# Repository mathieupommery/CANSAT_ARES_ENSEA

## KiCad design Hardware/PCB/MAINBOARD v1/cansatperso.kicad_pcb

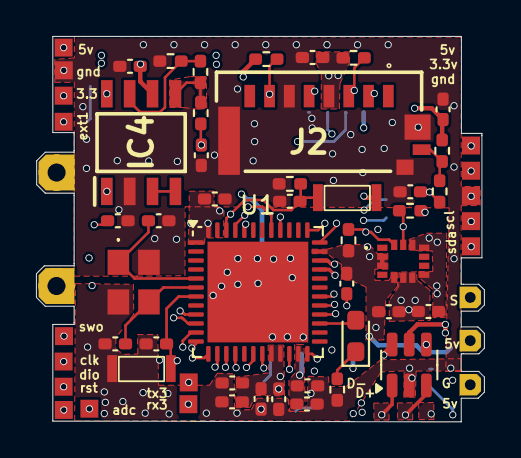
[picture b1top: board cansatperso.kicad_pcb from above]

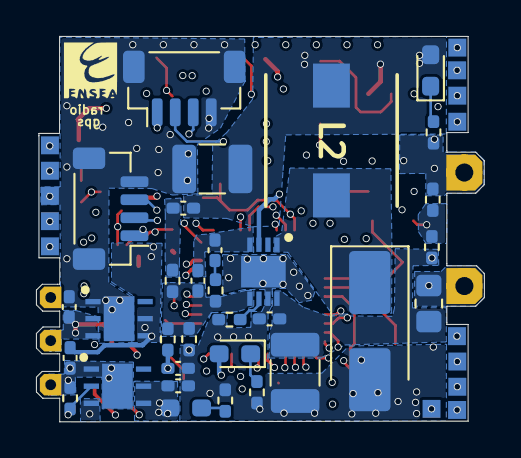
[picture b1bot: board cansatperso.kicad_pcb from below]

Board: 6 copper layers, 24.9 x 21.4 mm, 85 parts (34 on the bottom side), 44 nets.

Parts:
1, 1#2, 2, 2#2, 3, 3#2, 3#3, 4, 5, 6, 7, 7#2, 8: (no value)
C1, C4, C5, C6, C9, C16, C30: 100n; C_0402_1005Metric_Pad0.74x0.62mm_HandSolder
C2: 0.1u; C_0402_1005Metric_Pad0.74x0.62mm_HandSolder
C3, C7, C14, C32: 10n; C_0402_1005Metric_Pad0.74x0.62mm_HandSolder
C8, C10, C18, C19, C20, C21, C31: 1u; C_0402_1005Metric_Pad0.74x0.62mm_HandSolder
C11, C15: 4.7u; C_0402_1005Metric_Pad0.74x0.62mm_HandSolder
C12, C13: 16p; C_0402_1005Metric_Pad0.74x0.62mm_HandSolder
C17: 10u; C_0402_1005Metric_Pad0.74x0.62mm_HandSolder
C24: 10u; C_1210_3225Metric_Pad1.33x2.70mm_HandSolder
C25: 470n; C_0402_1005Metric_Pad0.74x0.62mm_HandSolder
C26: 22n; C_0402_1005Metric_Pad0.74x0.62mm_HandSolder
C27: 220p; C_0402_1005Metric_Pad0.74x0.62mm_HandSolder
C28: 3.3n; C_0402_1005Metric_Pad0.74x0.62mm_HandSolder
C29: 22u; C_1210_3225Metric_Pad1.33x2.70mm_HandSolder
D1, D3, D4, D5: LED; LED_0603_1608Metric_Pad1.05x0.95mm_HandSolder
D2: STPS3L40; D_SMB_Handsoldering
IC1: 2536030320001
IC2, IC5: LDO40LPU33RY; SON95P300X300X90-7N-D
IC3: L7981TR; SON50P300X300X100-9N-D
IC4: TSC102IDT; SOIC127P600X175-8N
J2: 47309-2651
J3: connecteur gps; JST_SH_BM04B-SRSS-TB_1x04-1MP_P1.00mm_Vertical
J4: connecteur radio; JST_SH_BM04B-SRSS-TB_1x04-1MP_P1.00mm_Vertical
L2: 22u; INDPM7373X340N
R1: 100k; R_0402_1005Metric_Pad0.72x0.64mm_HandSolder
R2, R5, R6, R22: 10k; R_0402_1005Metric_Pad0.72x0.64mm_HandSolder
R3, R17: 200R; R_0402_1005Metric_Pad0.72x0.64mm_HandSolder
R4, R11, R26: 1k; R_0402_1005Metric_Pad0.72x0.64mm_HandSolder
R7, R8, R9, R10: 47k; R_0402_1005Metric_Pad0.72x0.64mm_HandSolder
R15: 220k; R_0402_1005Metric_Pad0.72x0.64mm_HandSolder
R16: 3.3k; R_0402_1005Metric_Pad0.72x0.64mm_HandSolder
R18: 4.99k; R_0402_1005Metric_Pad0.72x0.64mm_HandSolder
R19: 680R; R_0402_1005Metric_Pad0.72x0.64mm_HandSolder
R20: 1.1k; R_0402_1005Metric_Pad0.72x0.64mm_HandSolder
R21: 20k; R_0402_1005Metric_Pad0.72x0.64mm_HandSolder
R23: 10m; R_0805_2012Metric_Pad1.20x1.40mm_HandSolder
R24: 100R; R_0402_1005Metric_Pad0.72x0.64mm_HandSolder
R25: 2k; R_0402_1005Metric_Pad0.72x0.64mm_HandSolder
SW1: RSTBTN; SW_KXT3
SW2: boot; SW_KXT3
U1: STM32G431CBUx; QFN-48-1EP_7x7mm_P0.5mm_EP5.6x5.6mm
U2: USBLC6-2SC6; SOT-23-6
Y1: Crystal_GND24_Small; MCSJK7U1200101080B10

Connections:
3.3VEN: C21.1, D4.2 (A), IC5.4 (VOUT), IC5.5 (VSENSE), J3.1, J4.1
+3.3V: 2.1, 7.1, 7#2.1, C1.1, C4.2, C5.2, C6.2, C7.2, C8.2, C9.2, C10.2, C11.1, C15.1, C16.1, C17.1, C20.1, D5.2 (A), IC1.2 (RSVD_1), IC1.3 (RSVD_2), IC1.5 (VDD_IO), IC1.8 (VDD), IC1.11 (RSVD_4), IC1.12 (CS), IC2.4 (VOUT), IC2.5 (VSENSE), J2.4, R5.1, R7.1, R8.1, R9.1, R10.2, SW2.2, U1.1 (VBAT), U1.20 (VREF+), U1.21 (VDDA), U1.23 (VDD), U1.35 (VDD), U1.48 (VDD)
+5V: 8.1, C18.1, C19.1, C28.1, C29.1, C31.1, D1.2 (A), IC2.2 (EN), IC2.3 (VIN), IC4.6 (VCC), IC5.3 (VIN), L2.2, R18.1, U2.5 (VBUS)
ADC1_IN2_CURR: C32.2, R24.1, U1.9 (PA1)
ADC1_IN3_VBAT: C30.2, R21.1, R22.2, U1.10 (PA2)
BAT+: IC4.8 (VP), R23.2
D+: U1.34 (PA12), U2.4 (I/O2)
D-: U1.33 (PA11), U2.6 (I/O1)
GND: 1.1, 6.1, C1.2, C2.1, C3.1, C4.1, C5.1, C6.1, C7.1, C8.1, C9.1, C10.1, C11.2, C12.2, C13.1, C14.2, C15.2, C16.2, C17.2, C18.2, C19.2, C20.2, C21.2, C24.2, C25.2, C29.2, C30.1, C31.2, C32.1, D2.2 (A), IC1.6 (GND_1), IC1.7 (GND_2), IC2.1 (GND), IC2.7 (EP), IC3.7 (GND), IC3.9 (EP), IC4.2 (GND), IC5.1 (GND), IC5.7 (EP), J2.6, J2.9 (G1), J2.10 (G2), J2.12 (G4), J3.4, J3.MP, J4.4, J4.MP, R1.2, R2.2, R3.1, R4.1, R11.1, R15.2, R19.2, R20.1, R22.1, R26.1, SW1.1, U1.49 (VSS), U2.2 (GND), Y1.2, Y1.4
GPIO_EXTI1: 3.1, U1.18 (PB1)
I2C3_SCL_ACCEL: 4.1, IC1.13 (SCL), R9.2, U1.30 (PA8)
I2C3_SDA_ACCEL: 5.1, IC1.14 (SDA), R10.1, U1.40 (PC11)
LPUART1_RX_RADIO: J4.2, U1.11 (PA3)
LPUART1_TX_RADIO: J4.3, U1.24 (PB11)
NRST: 3#2.1, 3#3.1, C2.2, SW1.2, U1.7 (PG10)
unnamed: C26.2, R16.1
unnamed: C28.2, R17.1
unnamed: D1.1 (K), R3.2
unnamed: D2.1 (K), IC3.1 (OUT), L2.1
unnamed: D3.2 (A), U1.27 (PB14)
unnamed: D3.1 (K), R20.2
unnamed: D4.1 (K), R4.2
unnamed: D5.1 (K), R11.2
unnamed: C26.1, C27.1, IC3.4 (COMP)
unnamed: C27.2, IC3.5 (FB), R16.2, R17.2, R18.2, R19.1
unnamed: IC3.6 (FSW), R15.1
unnamed: IC4.3 (A1), IC4.4 (A2)
unnamed: IC4.7 (A3), R25.1, R26.2
unnamed: IC4.5 (OUT), R24.2, R25.2
unnamed: J2.11 (G3), R5.2, R6.1
unnamed: C13.2, U1.5 (PF0), Y1.1
unnamed: C12.1, U1.6 (PF1), Y1.3
PWEN: IC5.2 (EN), R1.1, U1.28 (PB15)
SDDETECT: C14.1, R6.2, U1.19 (PB2)
SPI1_CS_SD: J2.2, U1.16 (PC4)
SPI1_MISO_SD: J2.7, R8.2, U1.14 (PA6)
SPI1_MOSI_SD: J2.3, R7.2, U1.15 (PA7)
SPI1_SCK_SD: J2.5, U1.13 (PA5)
SWCLK/I2C1_SDA: 1#2.1, U1.37 (PA14)
SWDIO: 2#2.1, U1.36 (PA13)
USART1_RX_GPS: J3.2, U1.45 (PB7)
USART1_TX_GPS: J3.3, U1.44 (PB6)
USART3_RX: C3.2, R2.1, SW2.1, U1.46 (PB8)
VIN: C24.1, C25.1, IC3.3 (EN), IC3.8 (V_CC), IC4.1 (VM), R21.2, R23.1

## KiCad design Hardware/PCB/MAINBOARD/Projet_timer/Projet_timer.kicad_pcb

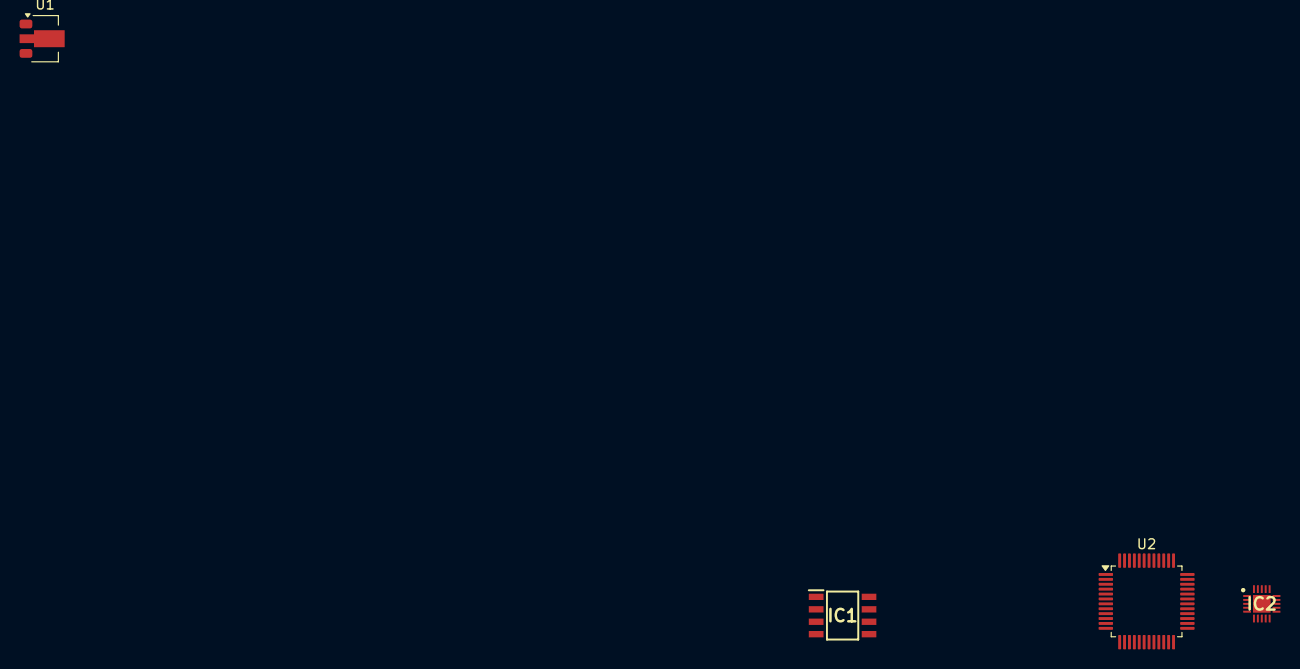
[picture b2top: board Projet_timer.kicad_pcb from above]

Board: 2 copper layers, 4 parts (0 on the bottom side), 3 nets, no tracks yet.

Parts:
IC1: AP1509-50SG-13; SOIC127P600X170-8N
IC2: TMC6300-LA-T; QFN40P300X300X90-21N
U1: AP130-33Y; SOT-89-3
U2: STM32G431C6Tx; LQFP-48_7x7mm_P0.5mm

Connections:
+8V: IC1.1 (VIN), U1.3 (VI)
GND: IC1.4 (SD), IC1.5 (GND_1), IC1.6 (GND_2), IC1.7 (GND_3), IC1.8 (GND_4), U1.2 (GND)
unnamed: U2.23 (VSS), U2.35 (VSS), U2.47 (VSS)

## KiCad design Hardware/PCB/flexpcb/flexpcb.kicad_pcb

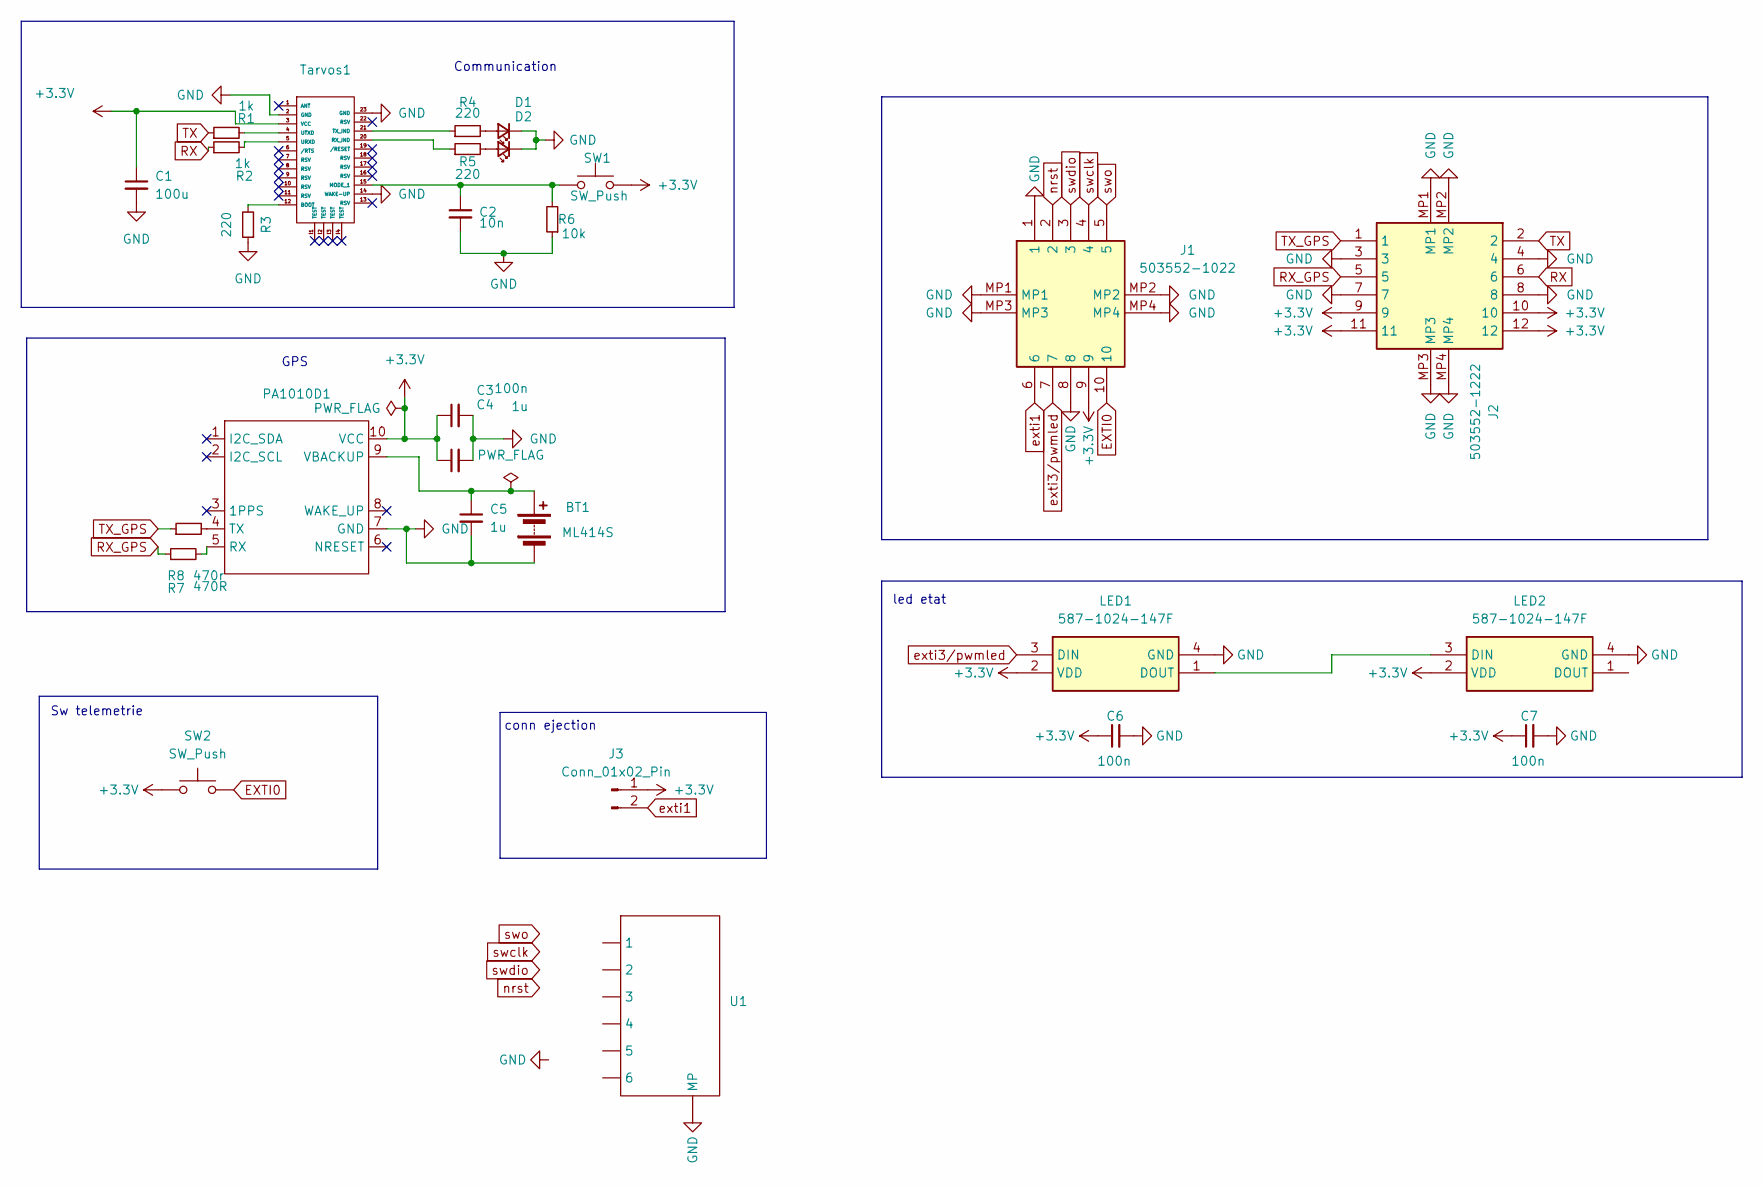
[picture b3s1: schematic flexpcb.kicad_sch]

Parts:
BT1: ML414S; MS421R-IV03E
C1: 100u; C_0805_2012Metric_Pad1.18x1.45mm_HandSolder
C2: 10n; C_0402_1005Metric
C3, C6, C7: 100n; C_0402_1005Metric
C4: 1u; C_0402_1005Metric
C5: 1u; C_0402_1005Metric_Pad0.74x0.62mm_HandSolder
D1, D2: LED_Small; LED_0603_1608Metric
J1: 503552-1022; 5035521022; Manufacturer_Part_Number 503552-1022; Mouser Part Number 538-503552-1022
J2: 503552-1222; 5035521222; Manufacturer_Part_Number 503552-1222; Mouser Part Number 538-503552-1222
J3: Conn_01x02_Pin
LED1, LED2: 587-1024-147F; Manufacturer_Part_Number 587-1024-147F
PA1010D1: PA1010D
R1, R2: 1k; R_0402_1005Metric
R3, R4, R5: 220; R_0402_1005Metric
R6: 10k; R_0402_1005Metric
R7: 470R; R_0402_1005Metric
R8: 470r; R_0402_1005Metric
SW1: SW_Push; PinHeader_1x02_P1.00mm_Horizontal
SW2: SW_Push
Tarvos1: Tarvos III
U1: (no value)

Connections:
+3.3V: C1.1, C3.1, C4.1, C6.1, C7.1, J1.9, J2.9, J2.10, J2.11, J2.12, J3.1, LED1.2 (VDD), LED2.2 (VDD), PA1010D1.10 (VCC), SW1.2, SW2.1, Tarvos1.3 (VCC); also elsewhere on the board
EXTI0: J1.10, SW2.2
GND: BT1.2 (-), C1.2, C2.2, C3.2, C4.2, C5.2, C6.2, C7.2, D1.1 (K), D2.1 (K), J1.1, J1.8, J1.MP1, J1.MP2, J1.MP3, J1.MP4, J2.3, J2.4, J2.7, J2.8, J2.MP1, J2.MP2, J2.MP3, J2.MP4, LED1.4 (GND), LED2.4 (GND), PA1010D1.7 (GND), R3.1, R6.1, Tarvos1.2 (GND), Tarvos1.14 (WAKE-UP), Tarvos1.23 (GND), U1., U1.5, U1.MP; also elsewhere on the board
unnamed: D1.2 (A), R4.2
unnamed: D2.2 (A), R5.2
unnamed: LED1.1 (DOUT), LED2.3 (DIN)
unnamed: PA1010D1.5 (RX), R7.2
unnamed: PA1010D1.4 (TX), R8.2
unnamed: BT1.1 (+), C5.1, PA1010D1.9 (VBACKUP)
unnamed: R3.2, Tarvos1.12 (BOOT)
unnamed: C2.1, R6.2, SW1.1, Tarvos1.15 (MODE_1)
unnamed: R5.1, Tarvos1.20 (RX_IND)
unnamed: R4.1, Tarvos1.21 (TX_IND)
unnamed: R2.2, Tarvos1.5 (URXD)
unnamed: R1.2, Tarvos1.4 (UTXD)
RX: J2.6, R2.1
RX_GPS: J2.5, R7.1
TX: J2.2, R1.1
TX_GPS: J2.1, R8.1
exti1: J1.6, J3.2; also elsewhere on the board
exti3/pwmled: J1.7, LED1.3 (DIN)
nrst: J1.2, U1.4
swclk: J1.4, U1.2
swdio: J1.3, U1.3
swo: J1.5, U1.1

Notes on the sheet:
conn ejection
Sw telemetrie
GPS
led etat
Communication

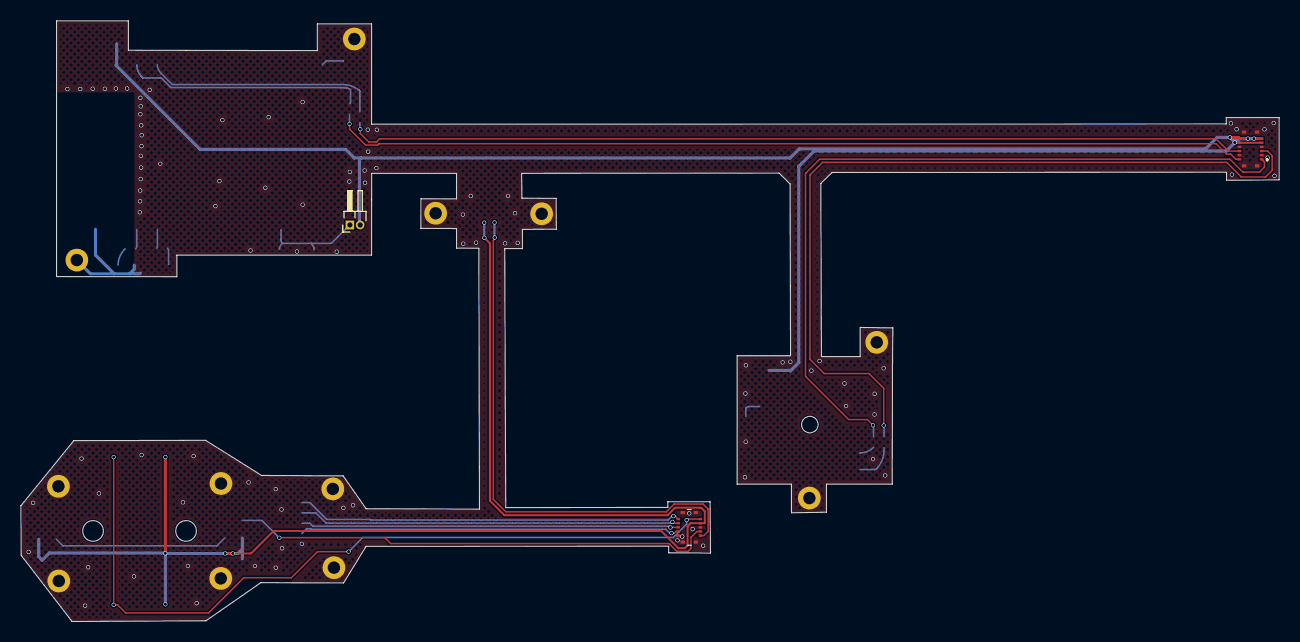
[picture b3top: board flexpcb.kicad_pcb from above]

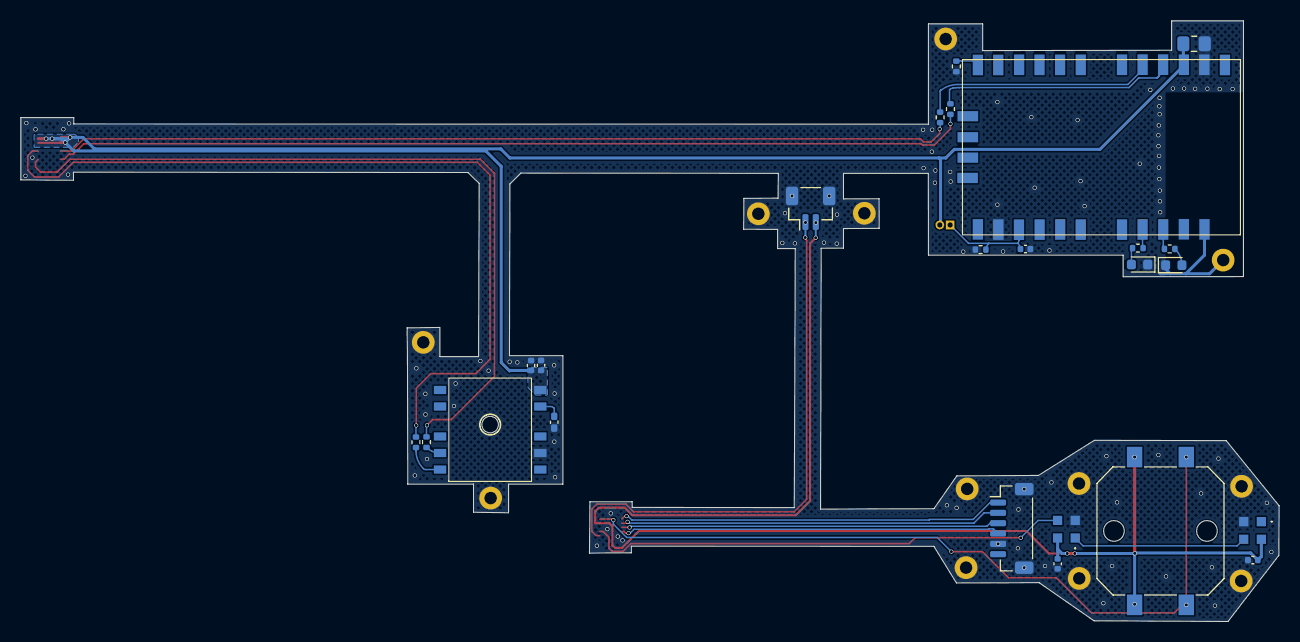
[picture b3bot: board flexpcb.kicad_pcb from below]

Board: 2 copper layers, 121.7 x 58.1 mm, 27 parts (24 on the bottom side), 25 nets.

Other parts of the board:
U2: JST_SH_BM02B-SRSS-TB_1x02-1MP_P1.00mm_Vertical

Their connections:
+3.3V: U2.2; also elsewhere on the board
GND: U2.MP; also elsewhere on the board
exti1: U2.1; also elsewhere on the board

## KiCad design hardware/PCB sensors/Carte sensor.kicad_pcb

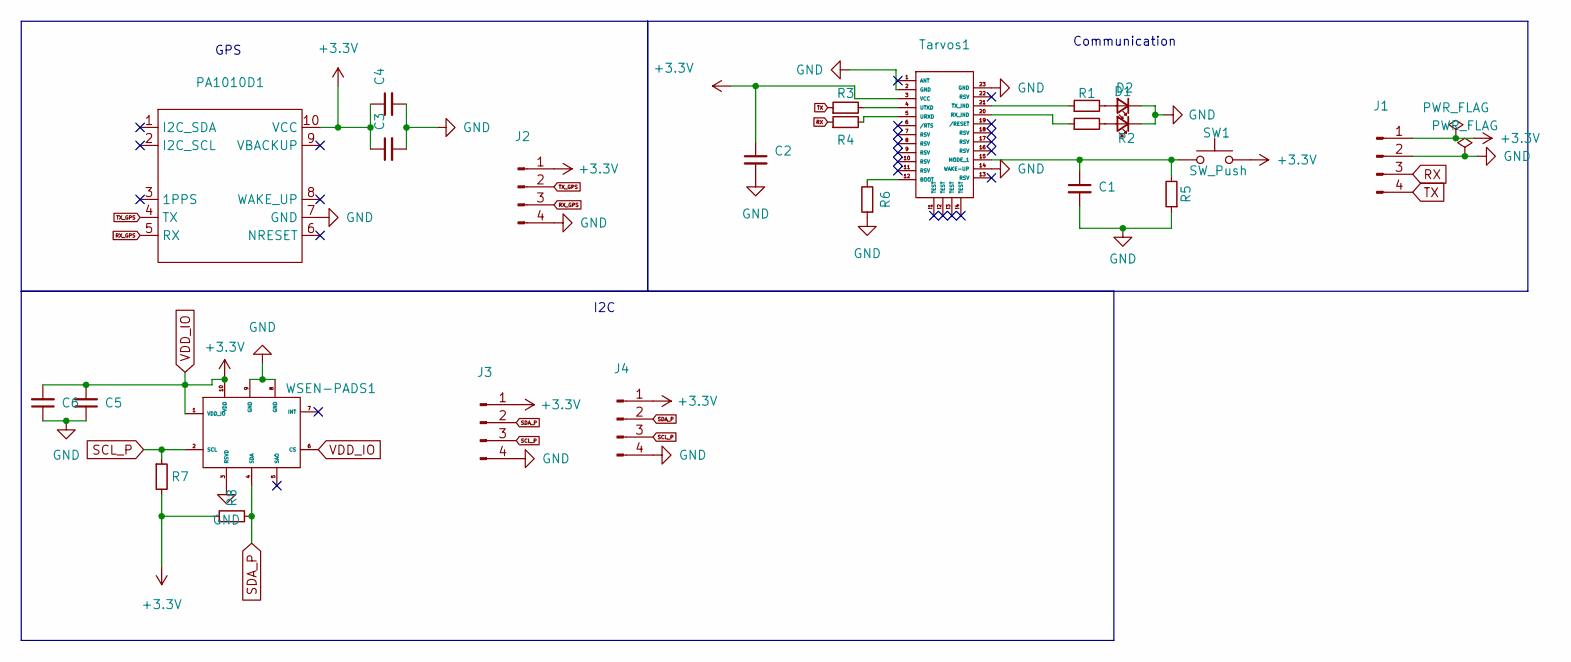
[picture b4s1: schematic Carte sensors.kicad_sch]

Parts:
C1: 10n; C_0402_1005Metric
C2, C3, C4: 100u; C_0402_1005Metric
C5: 4.7u; C_0402_1005Metric
C6: 100n; C_0402_1005Metric
D1, D2: LED_Small; LED_0603_1608Metric
J1, J2: Conn_01x04_Pin; JST_SH_BM04B-SRSS-TB_1x04-1MP_P1.00mm_Vertical
J3, J4: Conn_01x04_Pin; Wuerth_WR-WTB_64800411622_1x04_P1.50mm_Vertical
PA1010D1: PA1010D
R1, R2, R6: 220; R_0402_1005Metric
R3, R4: 1000; R_0402_1005Metric
R5: 10k; R_0402_1005Metric
R7, R8: 2.2k; R_0402_1005Metric
SW1: SW_Push; SW_PUSH_6mm
Tarvos1: Tarvos III
WSEN-PADS1: WSEN-PADS

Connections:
GND: C1.2, C2.2, C3.2, C4.2, C5.1, C6.1, D1.1 (K), D2.1 (K), J1.2, J2.4, J3.4, J4.4, PA1010D1.7 (GND), R5.1, R6.1, Tarvos1.2 (GND), Tarvos1.14 (WAKE-UP), Tarvos1.23 (GND), WSEN-PADS1.3 (RSVD), WSEN-PADS1.8 (GND), WSEN-PADS1.9 (GND)
unnamed: D1.2 (A), R1.2
unnamed: D2.2 (A), R2.2
unnamed: R6.2, Tarvos1.12 (BOOT)
unnamed: C1.1, R5.2, SW1.1, Tarvos1.15 (MODE_1)
unnamed: R2.1, Tarvos1.20 (RX_IND)
unnamed: R1.1, Tarvos1.21 (TX_IND)
unnamed: R4.2, Tarvos1.5 (URXD)
unnamed: R3.2, Tarvos1.4 (UTXD)
RX: J1.3, R4.1
RX_GPS: J2.3, PA1010D1.5 (RX)
SCL_P: J3.3, J4.3, R7.1, WSEN-PADS1.2 (SCL)
SDA_P: J3.2, J4.2, R8.2, WSEN-PADS1.4 (SDA)
TX: J1.4, R3.1
TX_GPS: J2.2, PA1010D1.4 (TX)
VDD_IO: C2.1, C3.1, C4.1, C5.2, C6.2, J1.1, J2.1, J3.1, J4.1, PA1010D1.10 (VCC), R7.2, R8.1, SW1.2, Tarvos1.3 (VCC), WSEN-PADS1.1 (VDD_IO), WSEN-PADS1.6 (CS), WSEN-PADS1.10 (VDD)

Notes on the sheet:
Communication
GPS
I2C

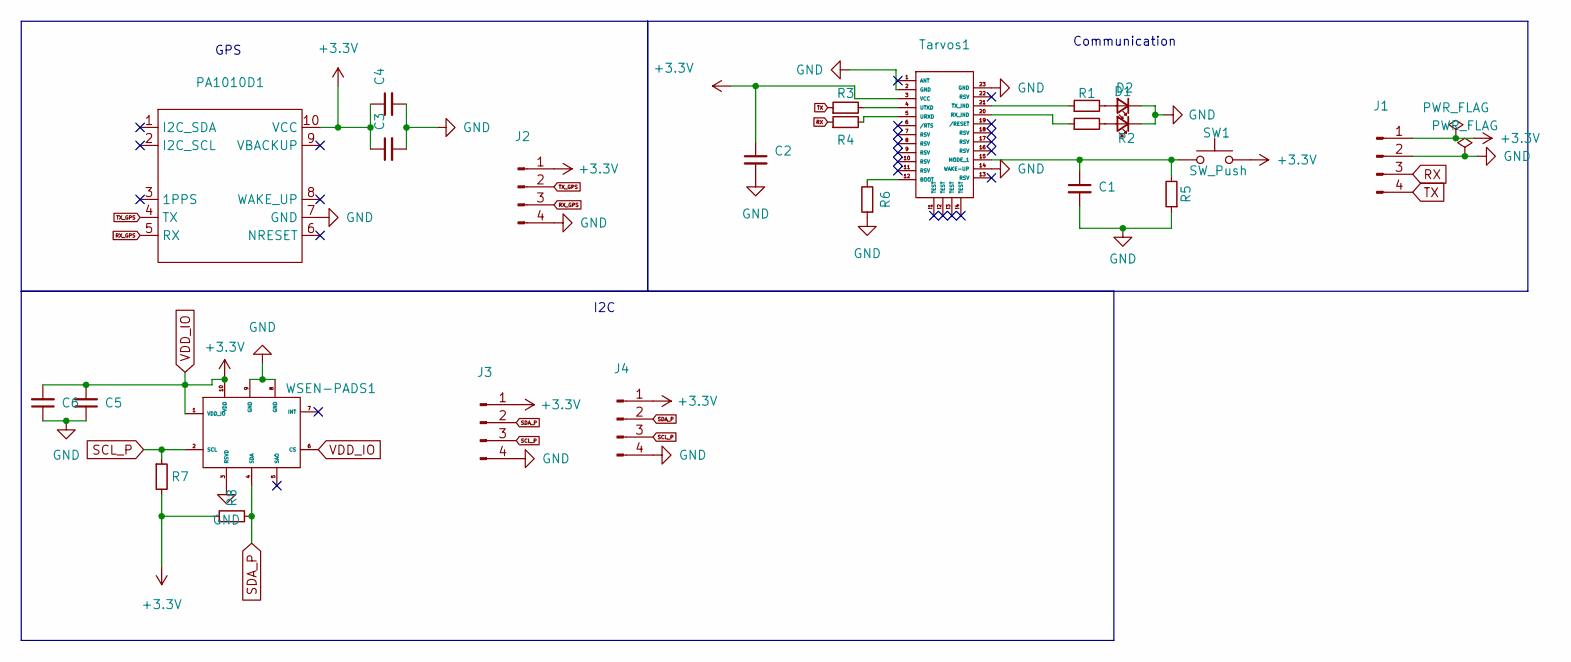
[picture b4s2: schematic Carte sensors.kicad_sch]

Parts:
C1: 10n; C_0402_1005Metric
C2, C3, C4: 100u; C_0402_1005Metric
C5: 4.7u; C_0402_1005Metric
C6: 100n; C_0402_1005Metric
D1, D2: LED_Small; LED_0603_1608Metric
J1, J2: Conn_01x04_Pin; JST_SH_BM04B-SRSS-TB_1x04-1MP_P1.00mm_Vertical
J3, J4: Conn_01x04_Pin; Wuerth_WR-WTB_64800411622_1x04_P1.50mm_Vertical
PA1010D1: PA1010D
R1, R2, R6: 220; R_0402_1005Metric
R3, R4: 1000; R_0402_1005Metric
R5: 10k; R_0402_1005Metric
R7, R8: 2.2k; R_0402_1005Metric
SW1: SW_Push; SW_PUSH_6mm
Tarvos1: Tarvos III
WSEN-PADS1: WSEN-PADS

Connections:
GND: C1.2, C2.2, C3.2, C4.2, C5.1, C6.1, D1.1 (K), D2.1 (K), J1.2, J2.4, J3.4, J4.4, PA1010D1.7 (GND), R5.1, R6.1, Tarvos1.2 (GND), Tarvos1.14 (WAKE-UP), Tarvos1.23 (GND), WSEN-PADS1.3 (RSVD), WSEN-PADS1.8 (GND), WSEN-PADS1.9 (GND)
unnamed: D1.2 (A), R1.2
unnamed: D2.2 (A), R2.2
unnamed: R6.2, Tarvos1.12 (BOOT)
unnamed: C1.1, R5.2, SW1.1, Tarvos1.15 (MODE_1)
unnamed: R2.1, Tarvos1.20 (RX_IND)
unnamed: R1.1, Tarvos1.21 (TX_IND)
unnamed: R4.2, Tarvos1.5 (URXD)
unnamed: R3.2, Tarvos1.4 (UTXD)
RX: J1.3, R4.1
RX_GPS: J2.3, PA1010D1.5 (RX)
SCL_P: J3.3, J4.3, R7.1, WSEN-PADS1.2 (SCL)
SDA_P: J3.2, J4.2, R8.2, WSEN-PADS1.4 (SDA)
TX: J1.4, R3.1
TX_GPS: J2.2, PA1010D1.4 (TX)
VDD_IO: C2.1, C3.1, C4.1, C5.2, C6.2, J1.1, J2.1, J3.1, J4.1, PA1010D1.10 (VCC), R7.2, R8.1, SW1.2, Tarvos1.3 (VCC), WSEN-PADS1.1 (VDD_IO), WSEN-PADS1.6 (CS), WSEN-PADS1.10 (VDD)

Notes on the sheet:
Communication
GPS
I2C

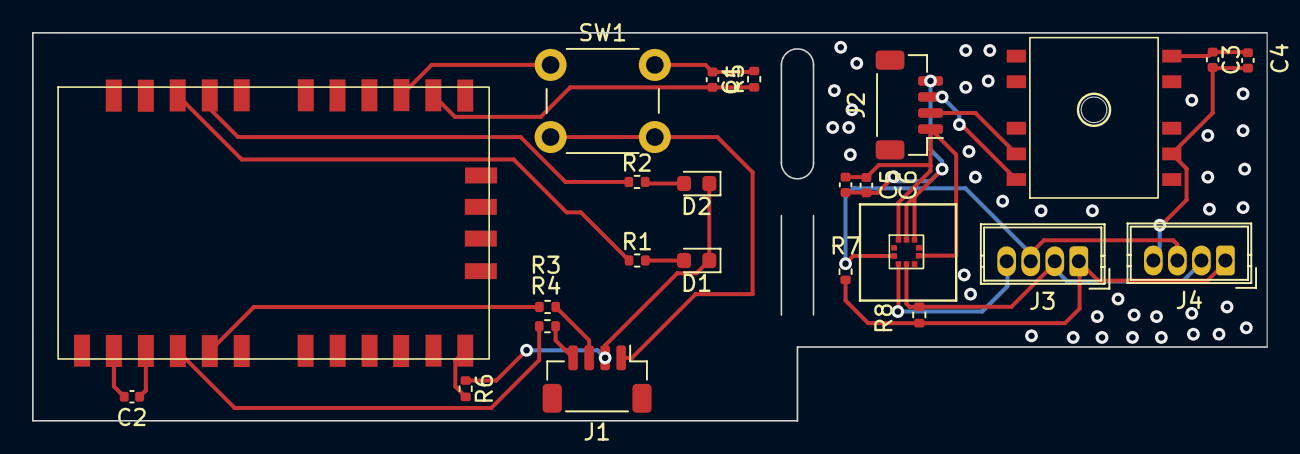
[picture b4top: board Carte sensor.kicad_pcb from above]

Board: 2 copper layers, 77.0 x 24.2 mm, 24 parts (0 on the bottom side), 16 nets.
